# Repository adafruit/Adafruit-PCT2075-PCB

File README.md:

## Adafruit PCT2075 Temperature Sensor PCB

<a href="http://www.adafruit.com/products/4369"><br/>
Click here to purchase one from the Adafruit shop</a>

PCB files for the Adafruit PCT2075 Temperature Sensor. 

Format is EagleCAD schematic and board layout
* https://www.adafruit.com/products/4369

### Description

The PCT2075 by NXP is a pin compatible drop in replacement for a very common I2C temperature sensor, the LM75. Compared to the LM75 however, the 11-bit ADC in the PCT2075 provides more precise measurements when compared to the LM75's 9-bit ADC. Additionally because the PCT2075 allows the address pins to work in three states (high, low, floating), you can have 27 PCT2075s on the same bus as opposed to only 8 for the LM75. Now you can finally measure the temperature the individual temperatures of the tentacles of three octopuses instead of just one!

Otherwise the two sensors are the same. The PCT2075 will report temperature and allow you to a set a high temperature threshold that the sensor will compare to the current temperature and raise an alert when the current temperature exceeds the threshold. There are also a few (metaphorical) knobs to twist to change the alerting and measurement behavior.

As with all Adafruit breakouts, we've done the work to make this handy temperature helper super easy to use. We've put it on a breakout board with the required support circuitry and connectors to make it easy to work with, and is now a trend we've added  [SparkFun Qwiic](https://www.sparkfun.com/qwiic) compatible [STEMMA QT](https://learn.adafruit.com/introducing-adafruit-stemma-qt) JST SH connectors that allow you to get going without needing to solder. Just use a [STEMMA QT adapter cable](https://www.adafruit.com/product/4209), plug it into your favorite micro or Blinka supported SBC and you're ready to rock!

"OK" you say "connections are one thing but how do I tell it what to do? (Not much of a) Surprise! We've written libraries for Arduino and CircuitPython with examples that make it super easy to integrate the PCT2075 with your project.

The PCT2075 is a handy and inexpensive temperature sensor that does one thing well. Try adding on to your project and have it keep an eye on the temperature and let you know when things get hot.

### License

Adafruit invests time and resources providing this open source design, please support Adafruit and open-source hardware by purchasing products from [Adafruit](https://www.adafruit.com)!

Designed by Bryan Siepert for Adafruit Industries.

Creative Commons Attribution/Share-Alike, all text above must be included in any redistribution. 
See license.txt for additional details.

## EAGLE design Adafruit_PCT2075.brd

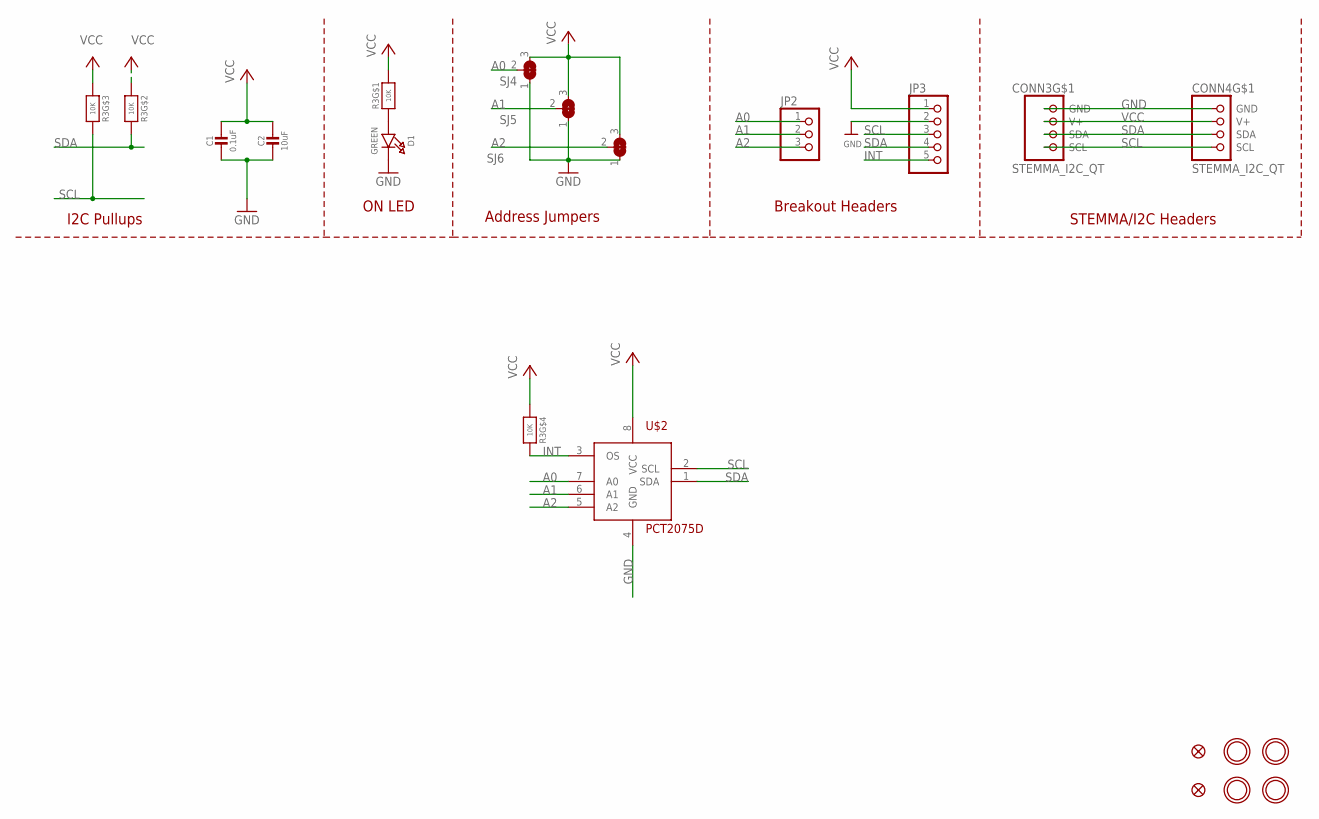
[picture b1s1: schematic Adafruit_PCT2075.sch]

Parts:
C1: 0.1uF; 0603-NO
C2: 10uF; 0805-NO
CONN3, CONN4: STEMMA_I2C_QT; JST_SH4
D1: GREEN; CHIPLED_0603_NOOUTLINE
FID3, FID4: FIDUCIAL_1MM
JP2: HEADER-1X3ROUND; 1X03_ROUND
JP3: HEADER-1X5ROUND; 1X05_ROUND
R3: 10K; RESPACK_4X0603
SJ4, SJ5, SJ6: SOLDERJUMPER_2WAY; SOLDERJUMPER_2WAY_OPEN_NOPASTE
U$1, U$17, U$19, U$21: MOUNTINGHOLE2.5; MOUNTINGHOLE_2.5_PLATED
U$2: PCT2075D; SOIC8_150MIL

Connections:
A0: JP2.1, SJ4.2, U$2.7 (A0)
A1: JP2.2, SJ5.2, U$2.6 (A1)
A2: JP2.3, SJ6.2, U$2.5 (A2)
GND: C1.2, C2.2, CONN3.1 (GND), CONN4.1 (GND), D1.C, JP3.2, SJ4.1, SJ5.1, SJ6.1, U$2.4 (GND)
INT: JP3.5, R3.5 (2), U$2.3 (OS)
unnamed: D1.A, R3.1
SCL: CONN3.4 (SCL), CONN4.4 (SCL), JP3.3, R3.6 (2), U$2.2 (SCL)
SDA: CONN3.3 (SDA), CONN4.3 (SDA), JP3.4, R3.7 (2), U$2.1 (SDA)
VCC: C1.1, C2.1, CONN3.2 (V+), CONN4.2 (V+), JP3.1, R3.2 (1), R3.3 (1), R3.4 (1), R3.8 (2), SJ4.3, SJ5.3, SJ6.3, U$2.8 (VCC)

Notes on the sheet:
I2C Pullups
STEMMA/I2C Headers
ON LED
Address Jumpers
Breakout Headers

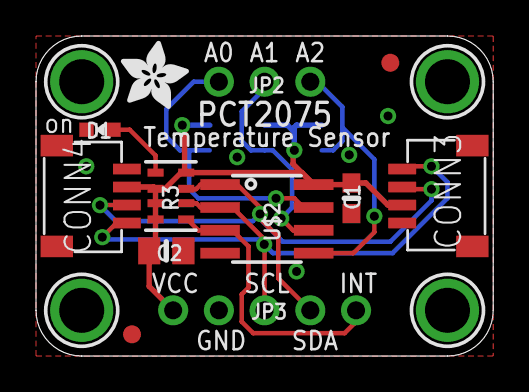
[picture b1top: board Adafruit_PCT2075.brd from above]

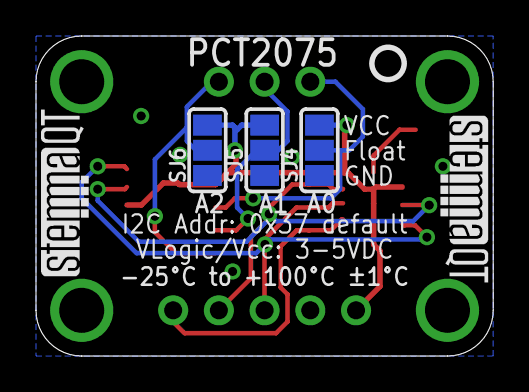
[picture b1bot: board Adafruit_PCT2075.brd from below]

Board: 2 copper layers, 25.4 x 17.8 mm, 22 parts (6 on the bottom side), 9 nets.

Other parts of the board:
U$22: ADAFRUIT_3.5MM
U$25: PCBFEAT-REV-040
U$30, U$31: STEMMAQT

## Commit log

2020-09-07 Fixed product image

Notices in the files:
parts and their libraries:
microbuilder: This work is placed in the public domain, and may be freely used for commercial and non-commercial work with the following conditions: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
